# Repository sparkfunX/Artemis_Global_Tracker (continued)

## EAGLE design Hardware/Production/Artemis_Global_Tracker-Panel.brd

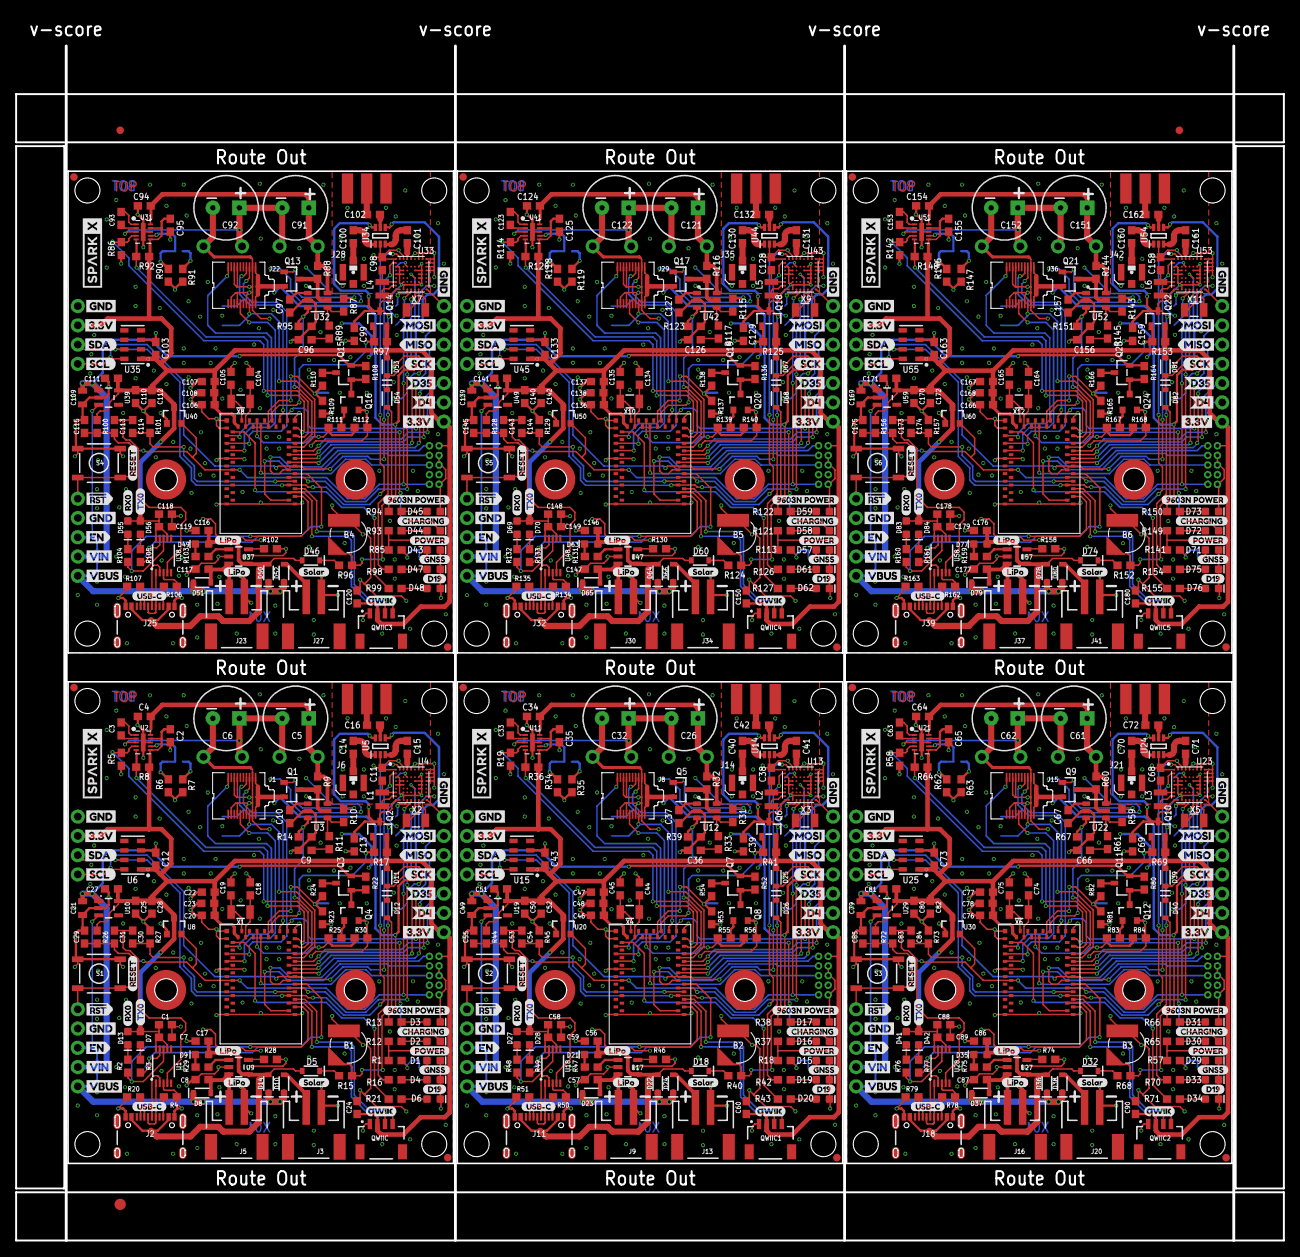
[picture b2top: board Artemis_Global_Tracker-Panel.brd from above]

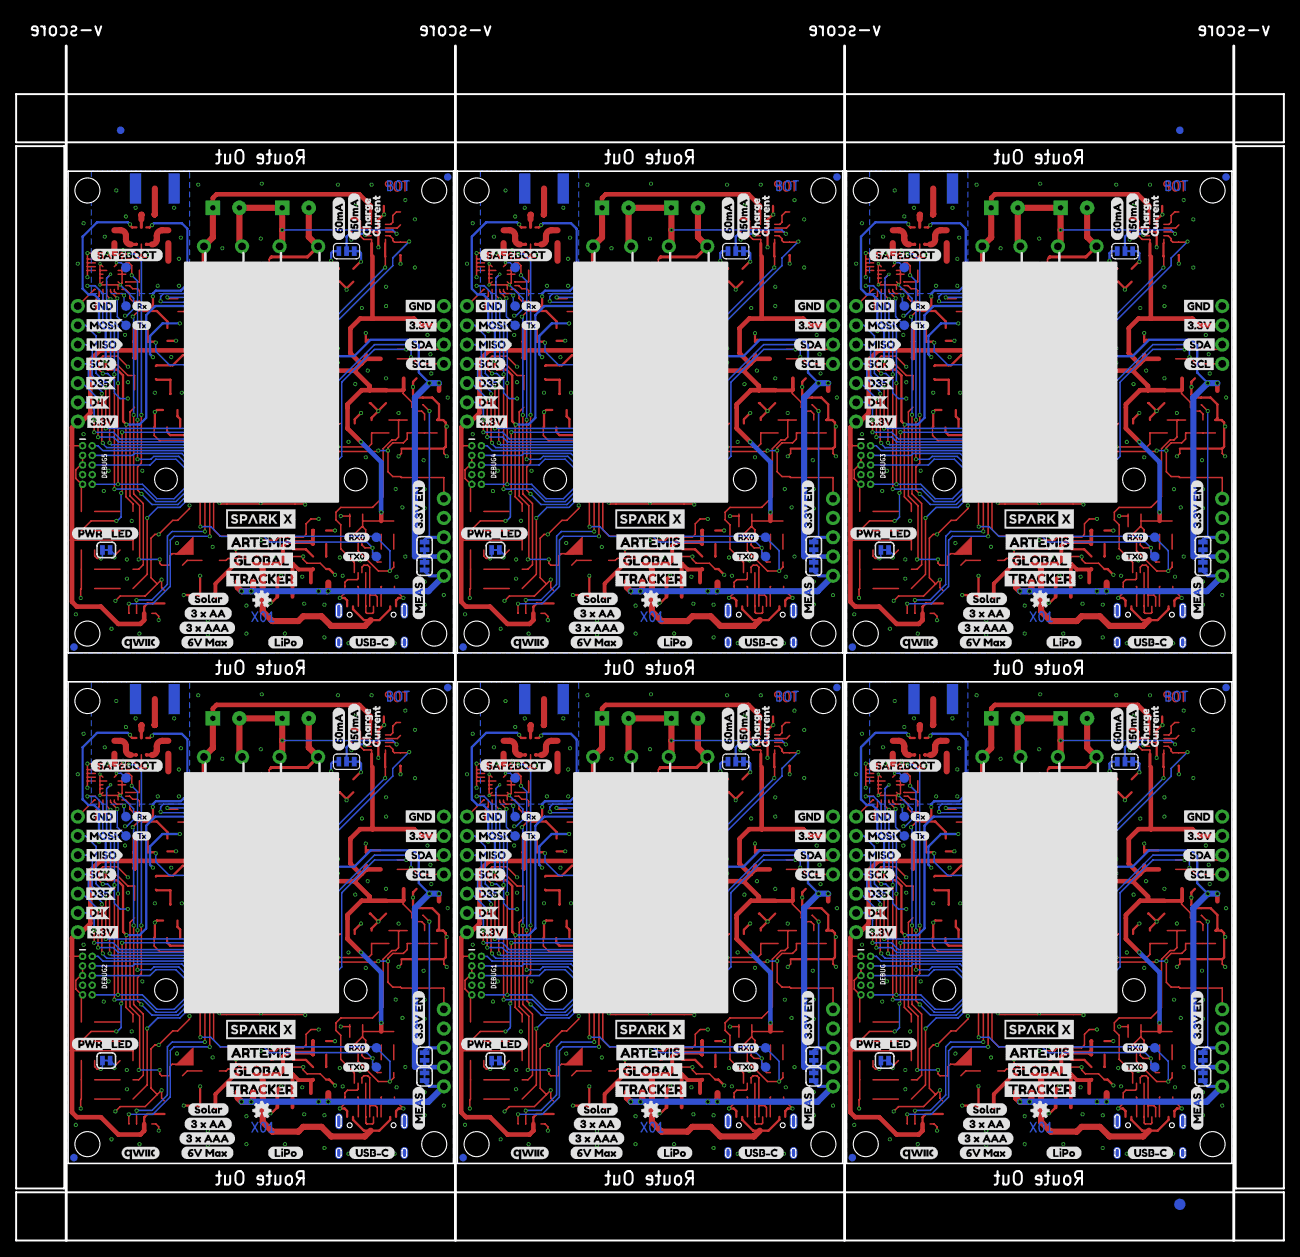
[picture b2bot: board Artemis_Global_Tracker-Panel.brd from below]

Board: 2 copper layers, 167.1 x 157.5 mm, 1200 parts (333 on the bottom side), 528 nets.

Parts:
3V3EN, 3V3EN1, 3V3EN2, 3V3EN3, 3V3EN4, 3V3EN5: JUMPER-SMT_2_NC_TRACE_SILK; SMT-JUMPER_2_NC_TRACE_SILK
5V1, 5V2, 5V3, 5V4, 5V5, 5V6: TEST-POINT3X5; PAD.03X.05
!RESET, !RESET1, !RESET2, !RESET3, !RESET4, !RESET5: 1X01_NO_SILK
B1, B2, B3, B4, B5, B6: ML414H_IV01E_BATTERY; ML414H_IV01E
C1, C9, C36, C58, C66, C88, C96, C118, C126, C148, C156, C178: 10nF; 0603
C2, C35, C65, C95, C125, C155: 2.2uF; 0603
C3, C10, C23, C24, C27, C33, C37, C48, C51, C60, C63, C67, C78, C81, C90, C93, C97, C108, C111, C120, C123, C127, C138, C141, C150, C153, C157, C168, C171, C180: 1.0uF; 0603
C4, C12, C34, C43, C64, C73, C94, C103, C124, C133, C154, C163: 0.22uF; 0603
C5, C6, C26, C32, C61, C62, C91, C92, C121, C122, C151, C152: 1F 2.7V; CPOL-RADIAL-1F-2.7V
C7, C13, C20, C28, C30, C31, C39, C46, C52, C53, C54, C59, C69, C76, C82, C83, C84, C89, C99, C106, C112, C113, C114, C119, C129, C136, C142, C143, C144, C149, C159, C166, C172, C173, C174, C179: 0.1uF; 0603
C8, C11, C17, C38, C56, C57, C68, C86, C87, C98, C116, C117, C128, C146, C147, C158, C176, C177: 4.7uF; 0603
C14, C15, C16, C40, C41, C42, C70, C71, C72, C100, C101, C102, C130, C131, C132, C160, C161, C162: 100pF; 0603
C18, C19, C44, C45, C74, C75, C104, C105, C134, C135, C164, C165: 15pF; 0603
C21, C49, C79, C109, C139, C169: 22uF; 0805
C22, C47, C77, C107, C137, C167: 10uF; 0603
C25, C50, C80, C110, C140, C170: 22uF; 0603
C29, C55, C85, C115, C145, C175: 1nF; 0603
D1, D7, D15, D28, D29, D42, D43, D56, D57, D70, D71, D84: GREEN; LED-0603
D2, D9, D13, D16, D21, D27, D30, D35, D41, D44, D49, D55, D58, D63, D69, D72, D77, D83: Yellow; LED-0603
D3, D17, D31, D45, D59, D73: RED; LED-0603
D4, D19, D33, D47, D61, D75: BLUE; LED-0603
D5, D8, D10, D11, D12, D14, D18, D22, D23, D24, D25, D26, D32, D36, D37, D38, D39, D40, D46, D50, D51, D52, D53, D54, D60, D64, D65, D66, D67, D68, D74, D78, D79, D80, D81, D82: 0.5A/40V/420mV; SOD-323
D6, D20, D34, D48, D62, D76: WHITE; LED-0603
DEBUG, DEBUG1, DEBUG2, DEBUG3, DEBUG4, DEBUG5: CORTEX_DEBUG; 2X5-PTH-1.27MM-NO_SILK
E$1, E$2, E$3, E$4: FIDUCIAL-1X2
E$5, E$6: FIDUCIAL-1.5X3
EN, EN1, EN2, EN3, EN4, EN5: 1X01_NO_SILK
GND, GND1, GND2, GND3, GND4, GND5: 1X01_NO_SILK
GPS_RX, GPS_RX1, GPS_RX2, GPS_RX3, GPS_RX4, GPS_RX5: TEST-POINT3X5; PAD.03X.05
GPS_TX, GPS_TX1, GPS_TX2, GPS_TX3, GPS_TX4, GPS_TX5: TEST-POINT3X5; PAD.03X.05
I2C, I2C1, I2C2, I2C3, I2C4, I2C5: PTH; 1X04_NO_SILK
J1, J8, J15, J22, J29, J36: IRIDIUM_9603N
J2, J11, J18, J25, J32, J39: USB-C; USB-C-16P
J3, J5, J9, J13, J16, J20, J23, J27, J30, J34, J37, J41: JST-2-SMD
J4, J10, J17, J24, J31, J38: 1X02_NO_SILK
J6, J14, J21, J28, J35, J42: U.FL
J7, J12, J19, J26, J33, J40: ANTENNA-GROUNDEDEDGE_SMA; SMA-EDGE
JP1, JP15, JP25, JP35, JP45, JP55: JUMPER-SMT_3_1-NC_TRACE_SILK; SMT-JUMPER_3_1-NC_TRACE_SILK
JP2, JP16, JP26, JP36, JP46, JP56: JUMPER-SMT_2_NC_TRACE_SILK; SMT-JUMPER_2_NC_TRACE_SILK
JP3, JP4, JP5, JP6, JP7, JP8, JP13, JP14, JP21, JP22, JP23, JP24, JP31, JP32, JP33, JP34, JP41, JP42, JP43, JP44, JP51, JP52, JP53, JP54: FIDUCIAL1X2; FIDUCIAL-1X2
JP9, JP10, JP11, JP12, JP17, JP18, JP19, JP20, JP27, JP28, JP29, JP30, JP37, JP38, JP39, JP40, JP47, JP48, JP49, JP50, JP57, JP58, JP59, JP60: STAND-OFF
L1, L2, L3, L4, L5, L6: 2.2uH; 0806
LOGO1, LOGO2, LOGO3, LOGO4, LOGO5, LOGO6: OSHW-LOGOMINI; OSHW-LOGO-MINI
MEAS, MEAS1, MEAS2, MEAS3, MEAS4, MEAS5: JUMPER-SMT_2_NC_TRACE_SILK; SMT-JUMPER_2_NC_TRACE_SILK
Q1, Q5, Q9, Q13, Q17, Q21: DMG3414U-7; SOT23-R
Q2, Q3, Q6, Q7, Q10, Q11, Q14, Q15, Q18, Q19, Q22, Q23: DMG3415U-7; SOT23-R
Q4, Q8, Q12, Q16, Q20, Q24: 600mA/40V; SOT23-3
QWIIC, QWIIC1, QWIIC2, QWIIC3, QWIIC4, QWIIC5: QWIIC_RIGHT_ANGLE; JST04_1MM_RA
R1, R2, R3, R12, R16, R18, R21, R25, R29, R37, R42, R43, R47, R48, R49, R55, R57, R65, R70, R71, R75, R76, R77, R83, R85, R93, R98, R99, R103, R104, R105, R111, R113, R121, R126, R127, R131, R132, R133, R139, R141, R149, R154, R155, R159, R160, R161, R167: 1k; 0603
R4, R20, R50, R51, R78, R79, R106, R107, R134, R135, R162, R163: 5.1k; 0603
R5, R14, R17, R19, R22, R23, R30, R39, R41, R52, R53, R56, R58, R67, R69, R80, R81, R84, R86, R95, R97, R108, R109, R112, R114, R123, R125, R136, R137, R140, R142, R151, R153, R164, R165, R168: 10k; 0603
R6, R34, R62, R90, R118, R146: 12k; 0603
R7, R35, R63, R91, R119, R147: 30.1k; 0603
R8, R26, R36, R44, R64, R72, R92, R100, R120, R128, R148, R156: 100k; 0603
R9, R32, R60, R88, R116, R144: 0.012R; 0603
R10, R11, R31, R33, R59, R61, R87, R89, R115, R117, R143, R145: 100; 0603
R13, R38, R66, R94, R122, R150: 2.2k; 0603
R15, R40, R68, R96, R124, R152: 62KOHM-0603-1/10W-5%; 0603
R24, R54, R82, R110, R138, R166: 20k; 0603
R27, R45, R73, R101, R129, R157: 220k; 0603
R28, R46, R74, R102, R130, R158: 2.0k; 0603
RX0, RX1, RX2, RX3, RX4, RX5, RX6, RX7, RX8, RX9, RX10, RX11: TEST-POINT3X5; PAD.03X.05
S1, S2, S3, S4, S5, S6: RESET; TACTILE_SWITCH_SMD_5.2MM
SAFEBOOT, SAFEBOOT1, SAFEBOOT2, SAFEBOOT3, SAFEBOOT4, SAFEBOOT5: TEST-POINT3X5; PAD.03X.05
SC1+, SC1+1, SC1+2, SC1+3, SC1+4, SC1+5, SC1-, SC1-1, SC1-2, SC1-3, SC1-4, SC1-5, SC2+, SC2+1, SC2+2, SC2+3, SC2+4, SC2+5, SC2-, SC2-1, SC2-2, SC2-3, SC2-4, SC2-5: 1X01_NO_SILK
SPARKX1, SPARKX2, SPARKX3, SPARKX4, SPARKX5, SPARKX6, SPARKX7, SPARKX8, SPARKX9, SPARKX10, SPARKX11, SPARKX12: SPARKX-LOGO4; SPARKX-MEDIUM
SPI, SPI1, SPI2, SPI3, SPI4, SPI5: 1X07_NO_SILK
TX0, TX1, TX2, TX3, TX4, TX5, TX6, TX7, TX8, TX9, TX10, TX11: TEST-POINT3X5; PAD.03X.05
U1, U18, U28, U38, U48, U58: CH340E_MSOP10; MSOP10
U2, U11, U21, U31, U41, U51: LTC3225EDDB#TRMPBF; DFN300X200-10L
U3, U12, U22, U32, U42, U52: ADM4210-1; TSOT6
U4, U13, U23, U33, U43, U53: UBLOX_ZOE_M8-0-10
U5, U14, U24, U34, U44, U54: AS179-92LF; SOT65P220X100-6N
U6, U15, U25, U35, U45, U55: MS8607-02BA01
U7, U16, U26, U36, U46, U56: ARTEMIS_MODULESMD; ARTEMIS_FP
U8, U20, U30, U40, U50, U60: V_SUPERVISORBD48K24G-TL; SSOP3
U9, U17, U27, U37, U47, U57: MCP73831; SOT23-5
U10, U19, U29, U39, U49, U59: 3.3V; SOT23-5
U$1, U$76, U$142, U$208, U$274, U$340: 60MA0
U$2, U$55, U$139, U$205, U$271, U$337: POWER0
U$3, U$12, U$17, U$22, U$28, U$52, U$80, U$81, U$134, U$137, U$146, U$147, U$200, U$203, U$212, U$213, U$266, U$269, U$278, U$279, U$332, U$335, U$344, U$345: GND1
U$4, U$8, U$20, U$21, U$24, U$54, U$82, U$83, U$133, U$138, U$148, U$149, U$199, U$204, U$214, U$215, U$265, U$270, U$280, U$281, U$331, U$336, U$346, U$347: 3#3V2
U$5, U$84, U$150, U$216, U$282, U$348: SCL0
U$6, U$85, U$151, U$217, U$283, U$349: SDA0
U$7, U$121, U$187, U$253, U$319, U$385: EN0
U$9, U$66, U$140, U$206, U$272, U$338: CHARGING0
U$10, U$75, U$141, U$207, U$273, U$339: 9603N_POWER0
U$11, U$131, U$197, U$263, U$329, U$395: QWIIC_4MM
U$13, U$77, U$143, U$209, U$275, U$341: 150MA0
U$14, U$78, U$144, U$210, U$276, U$342: CHARGE0
U$15, U$79, U$145, U$211, U$277, U$343: CURRENT0
U$16, U$38, U$95, U$113, U$161, U$179, U$227, U$245, U$293, U$311, U$359, U$377: TX00
U$18, U$31, U$86, U$87, U$152, U$153, U$218, U$219, U$284, U$285, U$350, U$351: SCK0
U$19, U$88, U$154, U$220, U$286, U$352: GNSS0
U$23, U$34, U$91, U$114, U$157, U$180, U$223, U$246, U$289, U$312, U$355, U$378: RX00
U$25, U$132, U$198, U$264, U$330, U$396: QWIIC_5MM
U$26, U$30, U$135, U$201, U$267, U$333: SCL9
U$27, U$51, U$136, U$202, U$268, U$334: SDA8
U$29, U$64, U$111, U$115, U$177, U$181, U$243, U$247, U$309, U$313, U$375, U$379: SOLAR0
U$32, U$89, U$155, U$221, U$287, U$353: 5#3V0
U$33, U$90, U$156, U$222, U$288, U$354: RX0
U$35, U$92, U$158, U$224, U$290, U$356: RX10
U$36, U$93, U$159, U$225, U$291, U$357: SAFEBOOT0
U$37, U$94, U$160, U$226, U$292, U$358: TX0
U$39, U$96, U$162, U$228, U$294, U$360: TX10
U$40, U$97, U$163, U$229, U$295, U$361: ARTEMIS0
U$41, U$98, U$164, U$230, U$296, U$362: GLOBAL0
U$42, U$99, U$165, U$231, U$297, U$363: TRACKER0
U$43, U$100, U$166, U$232, U$298, U$364: PWR_LED0
U$44, U$101, U$167, U$233, U$299, U$365: VBUS0
U$45, U$46, U$57, U$105, U$116, U$117, U$171, U$182, U$183, U$237, U$248, U$249, U$303, U$314, U$315, U$369, U$380, U$381: LIPO0
U$47, U$103, U$169, U$235, U$301, U$367: 3#3V_EN0
U$48, U$102, U$168, U$234, U$300, U$366: MEAS0
U$49, U$118, U$184, U$250, U$316, U$382: RESET0
U$50, U$104, U$170, U$236, U$302, U$368: D190
U$53, U$56, U$119, U$120, U$185, U$186, U$251, U$252, U$317, U$318, U$383, U$384: USB#C0
U$58, U$122, U$188, U$254, U$320, U$386: #RST0
U$59, U$106, U$172, U$238, U$304, U$370: GND0
U$60, U$107, U$173, U$239, U$305, U$371: VIN0
U$61, U$108, U$174, U$240, U$306, U$372: 3_X_AA0
U$62, U$109, U$175, U$241, U$307, U$373: 3_X_AAA0
U$63, U$110, U$176, U$242, U$308, U$374: 6V_MAX0
U$65, U$112, U$178, U$244, U$310, U$376: VIN#30
U$67, U$68, U$123, U$124, U$189, U$190, U$255, U$256, U$321, U$322, U$387, U$388: D350
U$69, U$70, U$125, U$126, U$191, U$192, U$257, U$258, U$323, U$324, U$389, U$390: MISO0
U$71, U$72, U$127, U$128, U$193, U$194, U$259, U$260, U$325, U$326, U$391, U$392: MOSI0
U$73, U$74, U$129, U$130, U$195, U$196, U$261, U$262, U$327, U$328, U$393, U$394: D40
VIN/1, VIN/2, VIN/3, VIN/4, VIN/5, VIN/6: TEST-POINT3X5; PAD.03X.05
X1, X2, X3, X4, X5, X6, X7, X8, X9, X10, X11, X12: 32.768kHz; CRYSTAL-SMD-3.2X1.5MM

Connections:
3.3V: C1.1, C2.1, C7.1, C12.1, C20.2, C22.1, C23.1, C24.1, C25.1, C27.1, C28.1, D7.A, D11.A, D13.A, DEBUG.1, I2C.2, Q2.2, QWIIC.2, R1.2, R8.2, R12.2, R17.2, R26.2, SPI.7, U1.7, U1.10, U2.6, U2.9, U6.1, U7.VDD@36, U7.VDD@37, U8.3, U10.5
3.3V1: C35.1, C43.1, C46.2, C47.1, C48.1, C50.1, C51.1, C52.1, C58.1, C59.1, C60.1, D25.A, D27.A, D28.A, DEBUG1.1, I2C1.2, Q6.2, QWIIC1.2, R18.2, R36.2, R37.2, R41.2, R44.2, SPI1.7, U11.6, U11.9, U15.1, U16.VDD@36, U16.VDD@37, U18.7, U18.10, U19.5, U20.3
3.3V2: C65.1, C73.1, C76.2, C77.1, C78.1, C80.1, C81.1, C82.1, C88.1, C89.1, C90.1, D39.A, D41.A, D42.A, DEBUG2.1, I2C2.2, Q10.2, QWIIC2.2, R57.2, R64.2, R65.2, R69.2, R72.2, SPI2.7, U21.6, U21.9, U25.1, U26.VDD@36, U26.VDD@37, U28.7, U28.10, U29.5, U30.3
3.3V3: C95.1, C103.1, C106.2, C107.1, C108.1, C110.1, C111.1, C112.1, C118.1, C119.1, C120.1, D53.A, D55.A, D56.A, DEBUG3.1, I2C3.2, Q14.2, QWIIC3.2, R85.2, R92.2, R93.2, R97.2, R100.2, SPI3.7, U31.6, U31.9, U35.1, U36.VDD@36, U36.VDD@37, U38.7, U38.10, U39.5, U40.3
3.3V4: C125.1, C133.1, C136.2, C137.1, C138.1, C140.1, C141.1, C142.1, C148.1, C149.1, C150.1, D67.A, D69.A, D70.A, DEBUG4.1, I2C4.2, Q18.2, QWIIC4.2, R113.2, R120.2, R121.2, R125.2, R128.2, SPI4.7, U41.6, U41.9, U45.1, U46.VDD@36, U46.VDD@37, U48.7, U48.10, U49.5, U50.3
3.3V5: C155.1, C163.1, C166.2, C167.1, C168.1, C170.1, C171.1, C172.1, C178.1, C179.1, C180.1, D81.A, D83.A, D84.A, DEBUG5.1, I2C5.2, Q22.2, QWIIC5.2, R141.2, R148.2, R149.2, R153.2, R156.2, SPI5.7, U51.6, U51.9, U55.1, U56.VDD@36, U56.VDD@37, U58.7, U58.10, U59.5, U60.3
3V3SW: C13.1, Q2.3, R16.2, U4.24, U4.25, U5.6
3V3SW1: C39.1, Q6.3, R42.2, U13.24, U13.25, U14.6
3V3SW2: C69.1, Q10.3, R70.2, U23.24, U23.25, U24.6
3V3SW3: C99.1, Q14.3, R98.2, U33.24, U33.25, U34.6
3V3SW4: C129.1, Q18.3, R126.2, U43.24, U43.25, U44.6
3V3SW5: C159.1, Q22.3, R154.2, U53.24, U53.25, U54.6
ANTENNA: C16.1, J7.SIG
ANTENNA1: C42.1, J12.SIG
ANTENNA2: C72.1, J19.SIG
ANTENNA3: C102.1, J26.SIG
ANTENNA4: C132.1, J33.SIG
ANTENNA5: C162.1, J40.SIG
ARTEMIS_!RESET: !RESET.1, C29.1, C31.2, DEBUG.10, R26.1, S1.3, S1.4, U4.20, U7.~RST, U8.2
ARTEMIS_!RESET1: !RESET1.1, C53.2, C55.1, DEBUG1.10, R44.1, S2.3, S2.4, U13.20, U16.~RST, U20.2
ARTEMIS_!RESET2: !RESET2.1, C83.2, C85.1, DEBUG2.10, R72.1, S3.3, S3.4, U23.20, U26.~RST, U30.2
ARTEMIS_!RESET3: !RESET3.1, C113.2, C115.1, DEBUG3.10, R100.1, S4.3, S4.4, U33.20, U36.~RST, U40.2
ARTEMIS_!RESET4: !RESET4.1, C143.2, C145.1, DEBUG4.10, R128.1, S5.3, S5.4, U43.20, U46.~RST, U50.2
ARTEMIS_!RESET5: !RESET5.1, C173.2, C175.1, DEBUG5.10, R156.1, S6.3, S6.4, U53.20, U56.~RST, U60.2
ARTEMIS_!RTS!: C30.1, C31.1, U1.4
ARTEMIS_!RTS!1: C53.1, C54.1, U18.4
ARTEMIS_!RTS!2: C83.1, C84.1, U28.4
ARTEMIS_!RTS!3: C113.1, C114.1, U38.4
ARTEMIS_!RTS!4: C143.1, C144.1, U48.4
ARTEMIS_!RTS!5: C173.1, C174.1, U58.4
ARTEMIS_BOOT: C30.2, R27.2, U7.BOOT
ARTEMIS_BOOT1: C54.2, R45.2, U16.BOOT
ARTEMIS_BOOT2: C84.2, R73.2, U26.BOOT
ARTEMIS_BOOT3: C114.2, R101.2, U36.BOOT
ARTEMIS_BOOT4: C144.2, R129.2, U46.BOOT
ARTEMIS_BOOT5: C174.2, R157.2, U56.BOOT
ARTEMIS_D1: DEBUG1.6, U16.~AD33/SWO
ARTEMIS_D2: SPI1.5, U16.~AD35
ARTEMIS_D3: R53.1, R54.2, U16.~AD13, VIN/1.P$1
ARTEMIS_D4: SPI.6, U7.~D4
ARTEMIS_D5: R43.2, U16.~D19
ARTEMIS_D5_SCK: SPI.4, U7.~D5
ARTEMIS_D5_SCK1: SPI1.4, U16.~D5
ARTEMIS_D5_SCK2: SPI2.4, U26.~D5
ARTEMIS_D5_SCK3: SPI3.4, U36.~D5
ARTEMIS_D5_SCK4: SPI4.4, U46.~D5
ARTEMIS_D5_SCK5: SPI5.4, U56.~D5
ARTEMIS_D6: J8.19, U16.~D18
ARTEMIS_D6_MISO: SPI.3, U7.~D6
ARTEMIS_D6_MISO1: SPI1.3, U16.~D6
ARTEMIS_D6_MISO2: SPI2.3, U26.~D6
ARTEMIS_D6_MISO3: SPI3.3, U36.~D6
ARTEMIS_D6_MISO4: SPI4.3, U46.~D6
ARTEMIS_D6_MISO5: SPI5.3, U56.~D6
ARTEMIS_D7: J8.7, RX3.P$1, U16.~D25
ARTEMIS_D7_MOSI: SPI.2, U7.D7
ARTEMIS_D7_MOSI1: SPI1.2, U16.D7
ARTEMIS_D7_MOSI2: SPI2.2, U26.D7
ARTEMIS_D7_MOSI3: SPI3.2, U36.D7
ARTEMIS_D7_MOSI4: SPI4.2, U46.D7
ARTEMIS_D7_MOSI5: SPI5.2, U56.D7
ARTEMIS_D8: R19.2, U11.4, U16.~D27
ARTEMIS_D8_SCL: I2C.4, U4.32, U6.8, U7.D8
ARTEMIS_D8_SCL1: I2C1.4, U13.32, U15.8, U16.D8
ARTEMIS_D8_SCL2: I2C2.4, U23.32, U25.8, U26.D8
ARTEMIS_D8_SCL3: I2C3.4, U33.32, U35.8, U36.D8
ARTEMIS_D8_SCL4: I2C4.4, U43.32, U45.8, U46.D8
ARTEMIS_D8_SCL5: I2C5.4, U53.32, U55.8, U56.D8
ARTEMIS_D9: SPI1.6, U16.~D4
ARTEMIS_D9_SDA: I2C.3, U4.2, U6.7, U7.D9
ARTEMIS_D9_SDA1: I2C1.3, U13.2, U15.7, U16.D9
ARTEMIS_D9_SDA2: I2C2.3, U23.2, U25.7, U26.D9
ARTEMIS_D9_SDA3: I2C3.3, U33.2, U35.7, U36.D9
ARTEMIS_D9_SDA4: I2C4.3, U43.2, U45.7, U46.D9
ARTEMIS_D9_SDA5: I2C5.3, U53.2, U55.7, U56.D9
ARTEMIS_D10: U4.50, U7.D10
ARTEMIS_D11: U13.50, U16.D10
ARTEMIS_D12: J8.5, U16.D17
ARTEMIS_D13: R23.1, R24.2, U7.~AD13, VIN/3.P$1
ARTEMIS_D14: R39.1, U12.3, U16.~D22
ARTEMIS_D15: J8.6, TX3.P$1, U16.~D24
ARTEMIS_D16: Q6.1, R41.1, U16.~D26
ARTEMIS_D17: J1.5, U7.D17
ARTEMIS_D18: J1.19, U7.~D18
ARTEMIS_D19: R21.2, U7.~D19
ARTEMIS_D20: D16.C, R36.1, U11.5, U16.~D28
ARTEMIS_D21: J8.12, U16.D41
ARTEMIS_D22: R14.1, U3.3, U7.~D22
ARTEMIS_D23: R55.1, R56.1, U16.AD34
ARTEMIS_D24: J1.6, TX1.P$1, U7.~D24
ARTEMIS_D25: J1.7, RX1.P$1, U7.~D25
ARTEMIS_D26: Q2.1, R17.1, U7.~D26
ARTEMIS_D27: R5.2, U2.4, U7.~D27
ARTEMIS_D28: D2.C, R8.1, U2.5, U7.~D28
ARTEMIS_D29: DEBUG2.6, U26.~AD33/SWO
ARTEMIS_D30: SPI2.5, U26.~AD35
ARTEMIS_D31: R81.1, R82.2, U26.~AD13, VIN/2.P$1
ARTEMIS_D32: R71.2, U26.~D19
ARTEMIS_D33: DEBUG.6, U7.~AD33/SWO
ARTEMIS_D34: R25.1, R30.1, U7.AD34
ARTEMIS_D35: SPI.5, U7.~AD35
ARTEMIS_D36: J15.19, U26.~D18
ARTEMIS_D37: J15.7, RX5.P$1, U26.~D25
ARTEMIS_D38: R58.2, U21.4, U26.~D27
ARTEMIS_D39: SPI2.6, U26.~D4
ARTEMIS_D39_SCL1: QWIIC1.4, U16.~D39
ARTEMIS_D39_SCL2: QWIIC2.4, U26.~D39
ARTEMIS_D39_SCL3: QWIIC3.4, U36.~D39
ARTEMIS_D39_SCL4: QWIIC.4, U7.~D39
ARTEMIS_D39_SCL5: QWIIC4.4, U46.~D39
ARTEMIS_D39_SCL6: QWIIC5.4, U56.~D39
ARTEMIS_D40: U23.50, U26.D10
ARTEMIS_D40_SDA1: QWIIC1.3, U16.D40
ARTEMIS_D40_SDA2: QWIIC2.3, U26.D40
ARTEMIS_D40_SDA3: QWIIC3.3, U36.D40
ARTEMIS_D40_SDA4: QWIIC.3, U7.D40
ARTEMIS_D40_SDA5: QWIIC4.3, U46.D40
ARTEMIS_D40_SDA6: QWIIC5.3, U56.D40
ARTEMIS_D41: J1.12, U7.D41
ARTEMIS_D42: J15.5, U26.D17
ARTEMIS_D43: R67.1, U22.3, U26.~D22
ARTEMIS_D44: J15.6, TX5.P$1, U26.~D24
ARTEMIS_D45: Q10.1, R69.1, U26.~D26
ARTEMIS_D46: D30.C, R64.1, U21.5, U26.~D28
ARTEMIS_D47: J15.12, U26.D41
ARTEMIS_D48: R83.1, R84.1, U26.AD34
ARTEMIS_D49: DEBUG3.6, U36.~AD33/SWO
ARTEMIS_D50: SPI3.5, U36.~AD35
ARTEMIS_D51: R109.1, R110.2, U36.~AD13, VIN/4.P$1
ARTEMIS_D52: R99.2, U36.~D19
ARTEMIS_D53: J22.19, U36.~D18
ARTEMIS_D54: J22.7, RX7.P$1, U36.~D25
ARTEMIS_D55: R86.2, U31.4, U36.~D27
ARTEMIS_D56: SPI3.6, U36.~D4
ARTEMIS_D57: U33.50, U36.D10
ARTEMIS_D58: J22.5, U36.D17
ARTEMIS_D59: R95.1, U32.3, U36.~D22
ARTEMIS_D60: J22.6, TX7.P$1, U36.~D24
ARTEMIS_D61: Q14.1, R97.1, U36.~D26
ARTEMIS_D62: D44.C, R92.1, U31.5, U36.~D28
ARTEMIS_D63: J22.12, U36.D41
ARTEMIS_D64: R111.1, R112.1, U36.AD34
ARTEMIS_D65: DEBUG4.6, U46.~AD33/SWO
ARTEMIS_D66: SPI4.5, U46.~AD35
ARTEMIS_D67: R137.1, R138.2, U46.~AD13, VIN/5.P$1
ARTEMIS_D68: R127.2, U46.~D19
ARTEMIS_D69: J29.19, U46.~D18
ARTEMIS_D70: J29.7, RX9.P$1, U46.~D25
ARTEMIS_D71: R114.2, U41.4, U46.~D27
ARTEMIS_D72: SPI4.6, U46.~D4
ARTEMIS_D73: U43.50, U46.D10
ARTEMIS_D74: J29.5, U46.D17
ARTEMIS_D75: R123.1, U42.3, U46.~D22
ARTEMIS_D76: J29.6, TX9.P$1, U46.~D24
ARTEMIS_D77: Q18.1, R125.1, U46.~D26
ARTEMIS_D78: D58.C, R120.1, U41.5, U46.~D28
ARTEMIS_D79: J29.12, U46.D41
ARTEMIS_D80: R139.1, R140.1, U46.AD34
ARTEMIS_D81: DEBUG5.6, U56.~AD33/SWO
ARTEMIS_D82: SPI5.5, U56.~AD35
ARTEMIS_D83: R165.1, R166.2, U56.~AD13, VIN/6.P$1
ARTEMIS_D84: R155.2, U56.~D19
ARTEMIS_D85: J36.19, U56.~D18
ARTEMIS_D86: J36.7, RX11.P$1, U56.~D25
ARTEMIS_D87: R142.2, U51.4, U56.~D27
ARTEMIS_D88: SPI5.6, U56.~D4
ARTEMIS_D89: U53.50, U56.D10
ARTEMIS_D90: J36.5, U56.D17
ARTEMIS_D91: R151.1, U52.3, U56.~D22
ARTEMIS_D92: J36.6, TX11.P$1, U56.~D24
ARTEMIS_D93: Q22.1, R153.1, U56.~D26
ARTEMIS_D94: D72.C, R148.1, U51.5, U56.~D28
ARTEMIS_D95: J36.12, U56.D41
ARTEMIS_D96: R167.1, R168.1, U56.AD34
ARTEMIS_RX0: R2.1, RX0.P$1, U1.8, U7.RXI-0
ARTEMIS_RX1: R48.1, RX2.P$1, U16.RXI-0, U18.8
ARTEMIS_RX2: R76.1, RX4.P$1, U26.RXI-0, U28.8
ARTEMIS_RX3: R104.1, RX6.P$1, U36.RXI-0, U38.8
ARTEMIS_RX4: R132.1, RX8.P$1, U46.RXI-0, U48.8
ARTEMIS_RX5: R160.1, RX10.P$1, U56.RXI-0, U58.8
ARTEMIS_SWDCK: DEBUG.4, U7.SWDCK
ARTEMIS_SWDCK1: DEBUG1.4, U16.SWDCK
ARTEMIS_SWDCK2: DEBUG2.4, U26.SWDCK
ARTEMIS_SWDCK3: DEBUG3.4, U36.SWDCK
ARTEMIS_SWDCK4: DEBUG4.4, U46.SWDCK
ARTEMIS_SWDCK5: DEBUG5.4, U56.SWDCK
ARTEMIS_SWDIO: DEBUG.2, U7.SWDIO
ARTEMIS_SWDIO1: DEBUG1.2, U16.SWDIO
ARTEMIS_SWDIO2: DEBUG2.2, U26.SWDIO
ARTEMIS_SWDIO3: DEBUG3.2, U36.SWDIO
ARTEMIS_SWDIO4: DEBUG4.2, U46.SWDIO
ARTEMIS_SWDIO5: DEBUG5.2, U56.SWDIO
ARTEMIS_TX0: R3.1, TX0.P$1, U1.9, U7.TXO-0
ARTEMIS_TX1: R49.1, TX2.P$1, U16.TXO-0, U18.9
ARTEMIS_TX2: R77.1, TX4.P$1, U26.TXO-0, U28.9
ARTEMIS_TX3: R105.1, TX6.P$1, U36.TXO-0, U38.9
ARTEMIS_TX4: R133.1, TX8.P$1, U46.TXO-0, U48.9
ARTEMIS_TX5: R161.1, TX10.P$1, U56.TXO-0, U58.9
CC1: J11.B5, R50.2
CC2: J11.A5, R51.2
CC3: J2.B5, R4.2
CC4: J2.A5, R20.2
CC5: J18.B5, R78.2
CC6: J18.A5, R79.2
CC7: J25.B5, R106.2
CC8: J25.A5, R107.2
CC9: J32.B5, R134.2
CC10: J32.A5, R135.2
CC11: J39.B5, R162.2
CC12: J39.A5, R163.2
D+1: J11.A6, J11.B6, U18.1
D+2: J2.A6, J2.B6, U1.1
D+3: J18.A6, J18.B6, U28.1
D+4: J25.A6, J25.B6, U38.1
D+5: J32.A6, J32.B6, U48.1
D+6: J39.A6, J39.B6, U58.1
D-1: J11.A7, J11.B7, U18.2
D-2: J2.A7, J2.B7, U1.2
D-3: J18.A7, J18.B7, U28.2
D-4: J25.A7, J25.B7, U38.2
D-5: J32.A7, J32.B7, U48.2
D-6: J39.A7, J39.B7, U58.2
EXT_PWR: 5V3.P$1, J1.1, J1.2, Q1.2, R13.2, U5.4
EXT_PWR1: 5V1.P$1, J8.1, J8.2, Q5.2, R38.2, U14.4
EXT_PWR2: 5V2.P$1, J15.1, J15.2, Q9.2, R66.2, U24.4
EXT_PWR3: 5V4.P$1, J22.1, J22.2, Q13.2, R94.2, U34.4
EXT_PWR4: 5V5.P$1, J29.1, J29.2, Q17.2, R122.2, U44.4
EXT_PWR5: 5V6.P$1, J36.1, J36.2, Q21.2, R150.2, U54.4
GND: B1.-, C1.2, C2.2, C4.2, C6.-, C7.2, C8.2, C9.2, C10.2, C11.2, C12.2, C13.2, C17.2, C18.1, C19.1, C20.1, C21.2, C22.2, C23.2, C24.2, C25.2, C27.2, C28.2, C29.2, D1.C, D3.C, D4.C, D6.C, DEBUG.3, DEBUG.5, DEBUG.9, GND.1, I2C.1, J1.3, J1.4, J1.8, J1.13, J1.14, J1.15, J1.18, J1.HOLE1, J1.HOLE2, J2.GND, J2.GND2, J3.1, J5.1, J6.1, J6.2, J7.GND@0, J7.GND@1, J7.GND@2, J7.GND@3, Q4.2, QWIIC.1, R4.1, R5.1, R6.1, R7.2, R14.2, R20.1, R23.2, R27.1, R28.1, R30.2, S1.1, S1.2, SC2-.1, SPI.1, U1.3, U2.8, U2.11, U3.2, U4.1, U4.3, U4.5, U4.7, U4.8, U4.9, U4.10, U4.11, U4.12, U4.17, U4.23, U4.29, U4.31, U4.37, U4.38, U4.39, U4.40, U4.41, U4.44, U4.46, U4.47, U4.49, U5.2, U6.3, U7.GND@1, U7.GND@22, U7.GND@38, U7.GND@39, U7.GND@47, U7.GND@59, U8.1, U9.2, U10.2
GND1: B2.-, C32.-, C34.2, C35.2, C36.2, C37.2, C38.2, C39.2, C43.2, C44.1, C45.1, C46.1, C47.2, C48.2, C49.2, C50.2, C51.2, C52.2, C55.2, C56.2, C57.2, C58.2, C59.2, C60.2, D15.C, D17.C, D19.C, D20.C, DEBUG1.3, DEBUG1.5, DEBUG1.9, GND1.1, I2C1.1, J8.3, J8.4, J8.8, J8.13, J8.14, J8.15, J8.18, J8.HOLE1, J8.HOLE2, J9.1, J11.GND, J11.GND2, J12.GND@0, J12.GND@1, J12.GND@2, J12.GND@3, J13.1, J14.1, J14.2, Q8.2, QWIIC1.1, R19.1, R34.1, R35.2, R39.2, R45.1, R46.1, R50.1, R51.1, R53.2, R56.2, S2.1, S2.2, SC2-1.1, SPI1.1, U11.8, U11.11, U12.2, U13.1, U13.3, U13.5, U13.7, U13.8, U13.9, U13.10, U13.11, U13.12, U13.17, U13.23, U13.29, U13.31, U13.37, U13.38, U13.39, U13.40, U13.41, U13.44, U13.46, U13.47, U13.49, U14.2, U15.3, U16.GND@1, U16.GND@22, U16.GND@38, U16.GND@39, U16.GND@47, U16.GND@59, U17.2, U18.3, U19.2, U20.1
GND2: B3.-, C62.-, C64.2, C65.2, C66.2, C67.2, C68.2, C69.2, C73.2, C74.1, C75.1, C76.1, C77.2, C78.2, C79.2, C80.2, C81.2, C82.2, C85.2, C86.2, C87.2, C88.2, C89.2, C90.2, D29.C, D31.C, D33.C, D34.C, DEBUG2.3, DEBUG2.5, DEBUG2.9, GND2.1, I2C2.1, J15.3, J15.4, J15.8, J15.13, J15.14, J15.15, J15.18, J15.HOLE1, J15.HOLE2, J16.1, J18.GND, J18.GND2, J19.GND@0, J19.GND@1, J19.GND@2, J19.GND@3, J20.1, J21.1, J21.2, Q12.2, QWIIC2.1, R58.1, R62.1, R63.2, R67.2, R73.1, R74.1, R78.1, R79.1, R81.2, R84.2, S3.1, S3.2, SC2-2.1, SPI2.1, U21.8, U21.11, U22.2, U23.1, U23.3, U23.5, U23.7, U23.8, U23.9, U23.10, U23.11, U23.12, U23.17, U23.23, U23.29, U23.31, U23.37, U23.38, U23.39, U23.40, U23.41, U23.44, U23.46, U23.47, U23.49, U24.2, U25.3, U26.GND@1, U26.GND@22, U26.GND@38, U26.GND@39, U26.GND@47, U26.GND@59, U27.2, U28.3, U29.2, U30.1
GND3: B4.-, C92.-, C94.2, C95.2, C96.2, C97.2, C98.2, C99.2, C103.2, C104.1, C105.1, C106.1, C107.2, C108.2, C109.2, C110.2, C111.2, C112.2, C115.2, C116.2, C117.2, C118.2, C119.2, C120.2, D43.C, D45.C, D47.C, D48.C, DEBUG3.3, DEBUG3.5, DEBUG3.9, GND3.1, I2C3.1, J22.3, J22.4, J22.8, J22.13, J22.14, J22.15, J22.18, J22.HOLE1, J22.HOLE2, J23.1, J25.GND, J25.GND2, J26.GND@0, J26.GND@1, J26.GND@2, J26.GND@3, J27.1, J28.1, J28.2, Q16.2, QWIIC3.1, R86.1, R90.1, R91.2, R95.2, R101.1, R102.1, R106.1, R107.1, R109.2, R112.2, S4.1, S4.2, SC2-3.1, SPI3.1, U31.8, U31.11, U32.2, U33.1, U33.3, U33.5, U33.7, U33.8, U33.9, U33.10, U33.11, U33.12, U33.17, U33.23, U33.29, U33.31, U33.37, U33.38, U33.39, U33.40, U33.41, U33.44, U33.46, U33.47, U33.49, U34.2, U35.3, U36.GND@1, U36.GND@22, U36.GND@38, U36.GND@39, U36.GND@47, U36.GND@59, U37.2, U38.3, U39.2, U40.1
GND4: B5.-, C122.-, C124.2, C125.2, C126.2, C127.2, C128.2, C129.2, C133.2, C134.1, C135.1, C136.1, C137.2, C138.2, C139.2, C140.2, C141.2, C142.2, C145.2, C146.2, C147.2, C148.2, C149.2, C150.2, D57.C, D59.C, D61.C, D62.C, DEBUG4.3, DEBUG4.5, DEBUG4.9, GND4.1, I2C4.1, J29.3, J29.4, J29.8, J29.13, J29.14, J29.15, J29.18, J29.HOLE1, J29.HOLE2, J30.1, J32.GND, J32.GND2, J33.GND@0, J33.GND@1, J33.GND@2, J33.GND@3, J34.1, J35.1, J35.2, Q20.2, QWIIC4.1, R114.1, R118.1, R119.2, R123.2, R129.1, R130.1, R134.1, R135.1, R137.2, R140.2, S5.1, S5.2, SC2-4.1, SPI4.1, U41.8, U41.11, U42.2, U43.1, U43.3, U43.5, U43.7, U43.8, U43.9, U43.10, U43.11, U43.12, U43.17, U43.23, U43.29, U43.31, U43.37, U43.38, U43.39, U43.40, U43.41, U43.44, U43.46, U43.47, U43.49, U44.2, U45.3, U46.GND@1, U46.GND@22, U46.GND@38, U46.GND@39, U46.GND@47, U46.GND@59, U47.2, U48.3, U49.2, U50.1
GND5: B6.-, C152.-, C154.2, C155.2, C156.2, C157.2, C158.2, C159.2, C163.2, C164.1, C165.1, C166.1, C167.2, C168.2, C169.2, C170.2, C171.2, C172.2, C175.2, C176.2, C177.2, C178.2, C179.2, C180.2, D71.C, D73.C, D75.C, D76.C, DEBUG5.3, DEBUG5.5, DEBUG5.9, GND5.1, I2C5.1, J36.3, J36.4, J36.8, J36.13, J36.14, J36.15, J36.18, J36.HOLE1, J36.HOLE2, J37.1, J39.GND, J39.GND2, J40.GND@0, J40.GND@1, J40.GND@2, J40.GND@3, J41.1, J42.1, J42.2, Q24.2, QWIIC5.1, R142.1, R146.1, R147.2, R151.2, R157.1, R158.1, R162.1, R163.1, R165.2, R168.2, S6.1, S6.2, SC2-5.1, SPI5.1, U51.8, U51.11, U52.2, U53.1, U53.3, U53.5, U53.7, U53.8, U53.9, U53.10, U53.11, U53.12, U53.17, U53.23, U53.29, U53.31, U53.37, U53.38, U53.39, U53.40, U53.41, U53.44, U53.46, U53.47, U53.49, U54.2, U55.3, U56.GND@1, U56.GND@22, U56.GND@38, U56.GND@39, U56.GND@47, U56.GND@59, U57.2, U58.3, U59.2, U60.1
GNSS: C15.2, U4.4
GNSS1: C41.2, U13.4
GNSS2: C71.2, U23.4
GNSS3: C101.2, U33.4
GNSS4: C131.2, U43.4
GNSS5: C161.2, U53.4
IRIDIUM: C14.2, J6.FEED
IRIDIUM1: C40.2, J14.FEED
IRIDIUM2: C70.2, J21.FEED
IRIDIUM3: C100.2, J28.FEED
IRIDIUM4: C130.2, J35.FEED
IRIDIUM5: C160.2, J42.FEED
LTC3225_VOUT: C4.1, C5.+, R9.2, SC1+.1, U2.10, U3.6
LTC3225_VOUT1: C26.+, C34.1, R32.2, SC1+1.1, U11.10, U12.6
LTC3225_VOUT2: C61.+, C64.1, R60.2, SC1+2.1, U21.10, U22.6
LTC3225_VOUT3: C91.+, C94.1, R88.2, SC1+3.1, U31.10, U32.6
LTC3225_VOUT4: C121.+, C124.1, R116.2, SC1+4.1, U41.10, U42.6
LTC3225_VOUT5: C151.+, C154.1, R144.2, SC1+5.1, U51.10, U52.6
unnamed: C5.-, C6.+, SC1-.1, SC2+.1, U2.3
unnamed: JP1.3, R6.2
unnamed: JP2.2, R1.1
unnamed: JP1.1, R7.1
unnamed: D2.A, R12.1
unnamed: D3.A, R13.1
unnamed: C33.2, U11.2
unnamed: Q1.3, R9.1, U3.5
unnamed: C3.2, U2.2
unnamed: C3.1, U2.1
unnamed: JP1.2, U2.7
unnamed: Q1.1, R10.1
unnamed: R10.2, R11.1, U3.4
unnamed: C9.1, R11.2
unnamed: C10.1, U3.1
unnamed: L1.2, U4.26
unnamed: C11.1, L1.1, U4.27
unnamed: U4.18, X2.P$2
unnamed: U4.19, X2.P$1
unnamed: D5.C, R15.2
unnamed: D4.A, R16.1
unnamed: D13.C, R2.2
unnamed: D1.A, JP2.1
unnamed: D11.C, D12.C, U4.16
unnamed: SAFEBOOT.P$1, U4.34
unnamed: GPS_RX.P$1, U4.22
unnamed: GPS_TX.P$1, U4.21
unnamed: C14.1, U5.1
unnamed: C15.1, U5.3
unnamed: C16.2, U5.5
unnamed: C33.1, U11.1
unnamed: D7.C, R3.2
unnamed: JP15.2, U11.7
unnamed: C26.-, C32.+, SC1-1.1, SC2+1.1, U11.3
unnamed: D6.A, R21.1
unnamed: 3V3EN.2, EN.1, U10.3
unnamed: Q3.1, Q4.3, R22.1
unnamed: JP15.3, R34.2
unnamed: R28.2, U9.5
unnamed: D9.C, R29.2
unnamed: R29.1, U9.1
unnamed: JP15.1, R35.1
unnamed: D16.A, R37.1
unnamed: D17.A, R38.1
unnamed: Q5.3, R32.1, U12.5
unnamed: Q3.3, R24.1
unnamed: Q4.1, R25.2
unnamed: Q5.1, R31.1
unnamed: R31.2, R33.1, U12.4
unnamed: C36.1, R33.2
unnamed: C37.1, U12.1
unnamed: L2.2, U13.26
unnamed: C38.1, L2.1, U13.27
unnamed: U13.18, X3.P$2
unnamed: U13.19, X3.P$1
unnamed: D18.C, R40.2
unnamed: SAFEBOOT1.P$1, U13.34
unnamed: GPS_RX1.P$1, U13.22
unnamed: GPS_TX1.P$1, U13.21
unnamed: C40.1, U14.1
unnamed: C41.1, U14.3
unnamed: C42.2, U14.5
unnamed: D19.A, R42.1
unnamed: D20.A, R43.1
unnamed: R46.2, U17.5
unnamed: D21.C, R47.2
unnamed: R47.1, U17.1
unnamed: D25.C, D26.C, U13.16
unnamed: 3V3EN1.2, EN1.1, U19.3
unnamed: Q7.1, Q8.3, R52.1
unnamed: Q7.3, R54.1
unnamed: Q8.1, R55.2
unnamed: D27.C, R48.2
unnamed: D28.C, R49.2
unnamed: JP16.2, R18.1
unnamed: D15.A, JP16.1
unnamed: C63.2, U21.2
unnamed: C63.1, U21.1
unnamed: JP25.2, U21.7
unnamed: C61.-, C62.+, SC1-2.1, SC2+2.1, U21.3
unnamed: JP25.3, R62.2
unnamed: JP25.1, R63.1
unnamed: D30.A, R65.1
unnamed: D31.A, R66.1
unnamed: Q9.3, R60.1, U22.5
unnamed: Q9.1, R59.1
unnamed: R59.2, R61.1, U22.4
unnamed: C66.1, R61.2
unnamed: C67.1, U22.1
unnamed: L3.2, U23.26
unnamed: C68.1, L3.1, U23.27
unnamed: U23.18, X5.P$2
unnamed: U23.19, X5.P$1
unnamed: D32.C, R68.2
unnamed: SAFEBOOT2.P$1, U23.34
unnamed: GPS_RX2.P$1, U23.22
unnamed: GPS_TX2.P$1, U23.21
unnamed: C70.1, U24.1
unnamed: C71.1, U24.3
unnamed: C72.2, U24.5
unnamed: D33.A, R70.1
unnamed: D34.A, R71.1
unnamed: R74.2, U27.5
unnamed: D35.C, R75.2
unnamed: R75.1, U27.1
unnamed: D39.C, D40.C, U23.16
unnamed: 3V3EN2.2, EN2.1, U29.3
unnamed: Q11.1, Q12.3, R80.1
unnamed: Q11.3, R82.1
unnamed: Q12.1, R83.2
unnamed: D41.C, R76.2
unnamed: D42.C, R77.2
unnamed: JP26.2, R57.1
unnamed: D29.A, JP26.1
unnamed: C93.2, U31.2
unnamed: C93.1, U31.1
unnamed: JP35.2, U31.7
unnamed: C91.-, C92.+, SC1-3.1, SC2+3.1, U31.3
unnamed: JP35.3, R90.2
unnamed: JP35.1, R91.1
unnamed: D44.A, R93.1
unnamed: D45.A, R94.1
unnamed: Q13.3, R88.1, U32.5
unnamed: Q13.1, R87.1
unnamed: R87.2, R89.1, U32.4
unnamed: C96.1, R89.2
unnamed: C97.1, U32.1
unnamed: L4.2, U33.26
unnamed: C98.1, L4.1, U33.27
unnamed: U33.18, X7.P$2
unnamed: U33.19, X7.P$1
unnamed: D46.C, R96.2
unnamed: SAFEBOOT3.P$1, U33.34
unnamed: GPS_RX3.P$1, U33.22
unnamed: GPS_TX3.P$1, U33.21
unnamed: C100.1, U34.1
unnamed: C101.1, U34.3
unnamed: C102.2, U34.5
unnamed: D47.A, R98.1
unnamed: D48.A, R99.1
unnamed: R102.2, U37.5
unnamed: D49.C, R103.2
unnamed: R103.1, U37.1
unnamed: D53.C, D54.C, U33.16
unnamed: 3V3EN3.2, EN3.1, U39.3
unnamed: Q15.1, Q16.3, R108.1
unnamed: Q15.3, R110.1
unnamed: Q16.1, R111.2
unnamed: D55.C, R104.2
unnamed: D56.C, R105.2
unnamed: JP36.2, R85.1
unnamed: D43.A, JP36.1
unnamed: C123.2, U41.2
unnamed: C123.1, U41.1
unnamed: JP45.2, U41.7
unnamed: C121.-, C122.+, SC1-4.1, SC2+4.1, U41.3
unnamed: JP45.3, R118.2
unnamed: JP45.1, R119.1
unnamed: D58.A, R121.1
unnamed: D59.A, R122.1
unnamed: Q17.3, R116.1, U42.5
unnamed: Q17.1, R115.1
unnamed: R115.2, R117.1, U42.4
unnamed: C126.1, R117.2
unnamed: C127.1, U42.1
unnamed: L5.2, U43.26
unnamed: C128.1, L5.1, U43.27
unnamed: U43.18, X9.P$2
unnamed: U43.19, X9.P$1
unnamed: D60.C, R124.2
unnamed: SAFEBOOT4.P$1, U43.34
unnamed: GPS_RX4.P$1, U43.22
unnamed: GPS_TX4.P$1, U43.21
unnamed: C130.1, U44.1
unnamed: C131.1, U44.3
unnamed: C132.2, U44.5
unnamed: D61.A, R126.1
unnamed: D62.A, R127.1
unnamed: R130.2, U47.5
unnamed: D63.C, R131.2
unnamed: R131.1, U47.1
unnamed: D67.C, D68.C, U43.16
unnamed: 3V3EN4.2, EN4.1, U49.3
unnamed: Q19.1, Q20.3, R136.1
unnamed: Q19.3, R138.1
unnamed: Q20.1, R139.2
unnamed: D69.C, R132.2
unnamed: D70.C, R133.2
unnamed: JP46.2, R113.1
unnamed: D57.A, JP46.1
unnamed: C153.2, U51.2
unnamed: C153.1, U51.1
unnamed: JP55.2, U51.7
unnamed: C151.-, C152.+, SC1-5.1, SC2+5.1, U51.3
unnamed: JP55.3, R146.2
unnamed: JP55.1, R147.1
unnamed: D72.A, R149.1
unnamed: D73.A, R150.1
unnamed: Q21.3, R144.1, U52.5
unnamed: Q21.1, R143.1
unnamed: R143.2, R145.1, U52.4
unnamed: C156.1, R145.2
unnamed: C157.1, U52.1
unnamed: L6.2, U53.26
unnamed: C158.1, L6.1, U53.27
unnamed: U53.18, X11.P$2
unnamed: U53.19, X11.P$1
unnamed: D74.C, R152.2
unnamed: SAFEBOOT5.P$1, U53.34
unnamed: GPS_RX5.P$1, U53.22
unnamed: GPS_TX5.P$1, U53.21
unnamed: C160.1, U54.1
unnamed: C161.1, U54.3
unnamed: C162.2, U54.5
unnamed: D75.A, R154.1
unnamed: D76.A, R155.1
unnamed: R158.2, U57.5
unnamed: D77.C, R159.2
unnamed: R159.1, U57.1
unnamed: D81.C, D82.C, U53.16
unnamed: 3V3EN5.2, EN5.1, U59.3
unnamed: Q23.1, Q24.3, R164.1
unnamed: Q23.3, R166.1
unnamed: Q24.1, R167.2
unnamed: D83.C, R160.2
unnamed: D84.C, R161.2
unnamed: JP56.2, R141.1
unnamed: D71.A, JP56.1
VBUS: D8.C, D10.C, D14.C, J4.2, MEAS.1
VBUS1: D22.C, D23.C, D24.C, J10.2, MEAS1.1
VBUS2: D36.C, D37.C, D38.C, J17.2, MEAS2.1
VBUS3: D50.C, D51.C, D52.C, J24.2, MEAS3.1
VBUS4: D64.C, D65.C, D66.C, J31.2, MEAS4.1
VBUS5: D78.C, D79.C, D80.C, J38.2, MEAS5.1
VIN: 3V3EN.1, C21.1, J4.1, MEAS.2, Q3.2, R22.2, U10.1
VIN1: 3V3EN1.1, C49.1, J10.1, MEAS1.2, Q7.2, R52.2, U19.1
VIN2: 3V3EN2.1, C79.1, J17.1, MEAS2.2, Q11.2, R80.2, U29.1
VIN3: 3V3EN3.1, C109.1, J24.1, MEAS3.2, Q15.2, R108.2, U39.1
VIN4: 3V3EN4.1, C139.1, J31.1, MEAS4.2, Q19.2, R136.2, U49.1
VIN5: 3V3EN5.1, C169.1, J38.1, MEAS5.2, Q23.2, R164.2, U59.1
V_AAA: D10.A, J3.2
V_AAA1: D24.A, J13.2
V_AAA2: D38.A, J20.2
V_AAA3: D52.A, J27.2
V_AAA4: D66.A, J34.2
V_AAA5: D80.A, J41.2
V_BATT: C8.1, D8.A, J5.2, U9.3
V_BATT1: C57.1, D23.A, J9.2, U17.3
V_BATT2: C87.1, D37.A, J16.2, U27.3
V_BATT3: C117.1, D51.A, J23.2, U37.3
V_BATT4: C147.1, D65.A, J30.2, U47.3
V_BATT5: C177.1, D79.A, J37.2, U57.3
V_BCKP: B1.+, D12.A, R15.1
V_BCKP1: B2.+, D26.A, R40.1
V_BCKP2: B3.+, D40.A, R68.1
V_BCKP3: B4.+, D54.A, R96.1
V_BCKP4: B5.+, D68.A, R124.1
V_BCKP5: B6.+, D82.A, R152.1
V_USB: C17.1, D5.A, D9.A, D14.A, J2.VBUS1, J2.VBUS2, U9.4
V_USB1: C56.1, D18.A, D21.A, D22.A, J11.VBUS1, J11.VBUS2, U17.4
V_USB2: C86.1, D32.A, D35.A, D36.A, J18.VBUS1, J18.VBUS2, U27.4
V_USB3: C116.1, D46.A, D49.A, D50.A, J25.VBUS1, J25.VBUS2, U37.4
V_USB4: C146.1, D60.A, D63.A, D64.A, J32.VBUS1, J32.VBUS2, U47.4
V_USB5: C176.1, D74.A, D77.A, D78.A, J39.VBUS1, J39.VBUS2, U57.4
XTALI: C19.2, U7.XI, X1.P$1
XTALI1: C45.2, U16.XI, X4.P$1
XTALI2: C75.2, U26.XI, X6.P$1
XTALI3: C105.2, U36.XI, X8.P$1
XTALI4: C135.2, U46.XI, X10.P$1
XTALI5: C165.2, U56.XI, X12.P$1
XTALO: C18.2, U7.XO, X1.P$2
XTALO1: C44.2, U16.XO, X4.P$2
XTALO2: C74.2, U26.XO, X6.P$2
XTALO3: C104.2, U36.XO, X8.P$2
XTALO4: C134.2, U46.XO, X10.P$2
XTALO5: C164.2, U56.XO, X12.P$2

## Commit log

2020-05-13 Copying over PaulZC/Artemis_Global_Tracker
2020-05-15 Added product link
2020-05-19 Added the bus voltage correction factor
2020-06-07 Updated the links for the MS8607 library
2020-06-09 Added the binaries for the AFU
2020-06-13 Updating the Windows .exe. Now uses --noconsole.
2020-07-21 Added Production Test 6: RTC test
2020-07-21 Added Get IMEI to Example 9 (Get Time) to ease production testing
2020-07-22 Added Example18: Production Test Part Deux
    Example 18 check that the ZOE can obtain a 3D fix and that the Iridium modem can read satellite time. The AGT can be powered from a LiPo cell for this test. The white LED indicates success / failure.
2020-09-30 Adding SIV and altitude
2020-11-09 Updating the FAQs
2020-12-15 Corrections for deep sleep - to prevent RAM corruption
2021-05-08 Added message translator for binary SBD files.
2021-05-11 Added option in Message Translator to read messages from IMAP server, and updated README.
2021-06-16 Bugfix im message translator: added forgotten conversion factors.
2021-07-07 Bugfix in binary message contruction in example 16
2021-08-07 Updated examples 1-5 using v2.1.0 of the core
2021-08-08 Update examples 5-13. Example14 is work in progress.
2021-08-09 Update gnssON and gnssOFF
2021-08-09 Updating Example16 for Apollo3 v2.1 - compiles, ready for testing
2021-08-09 Example16 - updated and tested on Apollo3 v2.1.0
2021-08-09 Add updated binaries - compiled using v2.1.0 of Apollo3
2021-08-11 Add user function to be executed when a PHT alarm is set off.
2021-08-12 Add AGT_iridiumSleep_Test example to help diagnose #36
2021-08-12 Update AGT_iridiumSleep_Test
2021-08-12 Update gnssON and gnssOFF in remaining examples
2021-08-15 Add Examples 19 & 20
    Example19 allows control of the AGT via a simple Serial Terminal interface.
    Example20 reads the module information from the ZOE-M8Q.
2021-08-15 Update the README's. Add the binary for Example19
2021-08-25 v2.1: update the examples to correct issue 423 in the Apollo3 core
    https://github.com/sparkfun/Arduino_Apollo3/issues/423
2021-08-26 Update the example binaries using v3.0.5 of the IridiumSBDi2c library - changing the timing of beginSerialPort
2021-09-04 Bugfix regarding negative temperature measurements
2021-09-07 Adding modem.endSerialPort to the Iridium examples setup - to resolve #38 and hopefully #36 too
2021-09-24 Setting default measurement values to fill values outside valid range since they indicate invalid measurements
